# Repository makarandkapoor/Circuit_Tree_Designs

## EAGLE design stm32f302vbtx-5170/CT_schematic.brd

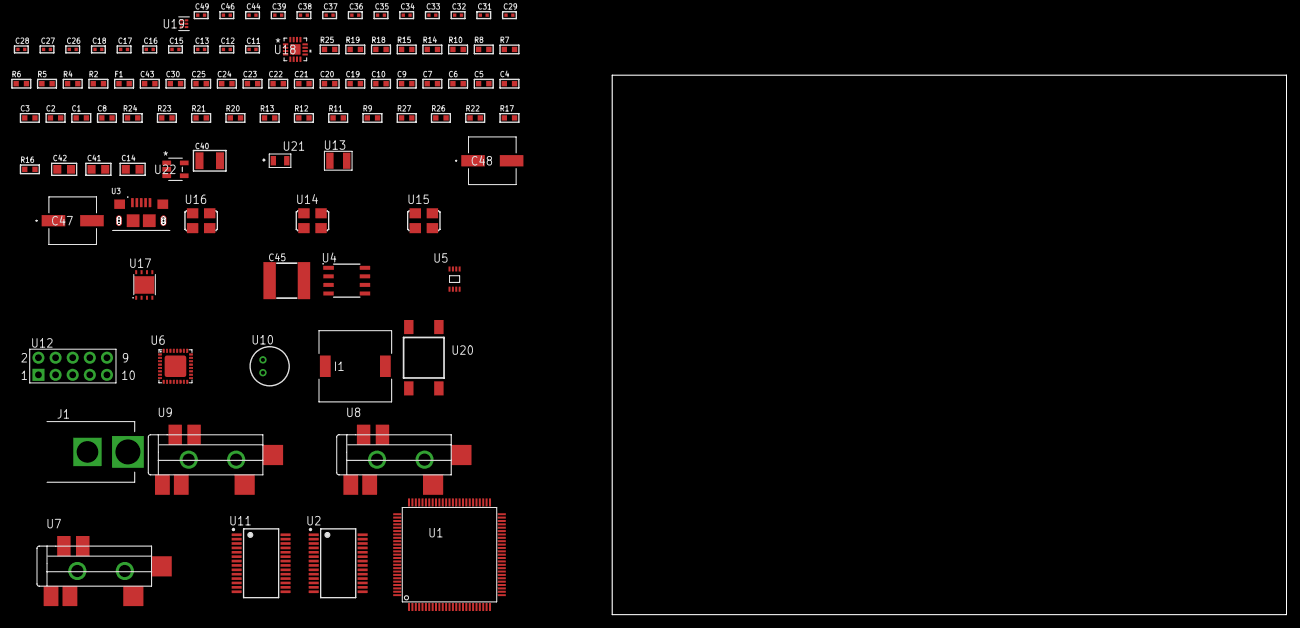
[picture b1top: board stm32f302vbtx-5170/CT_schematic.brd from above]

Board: 2 copper layers, 99 parts (0 on the bottom side), 69 nets, no tracks yet.

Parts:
C1, C10, C19, C20, C21, C22, C23, C24, C25, C30, C43: 1e-06; C0603
C2, C3, C4, C5, C6, C7: 1e-07; C0603
C8: 4.7e-06; C0603
C9: 1e-08; C0603
C11, C12: 1e-11; C0402
C13, C15, C16, C26, C27, C28, C29, C31, C32, C33, C34, C35, C44, C46: 1e-07; C0402
C14: 4.7e-06; C0805
C17, C18, C36, C37, C38, C39, C49: 1e-08; C0402
C40: 1e-05; C1210
C41, C42: 1e-05; C0805
C45: 6.8e-05; 2220
C47, C48: 0.0001; EXV-9H
F1: 240.0; L0603
I1: 5.2e-06; DR1040
J1: PJ-037B; PJ-037B_PACKAGE
R2, R19: 1000.0; R0603
R4, R10: 4700.0; R0603
R5, R6, R7, R8: 2200.0; R0603
R9, R11, R12, R13, R23, R24: 10000.0; R0603
R14, R15: 1270.0; R0603
R16, R17: 100000.0; R0603
R18: 200.0; R0603
R20: 20000.0; R0603
R21: 91000.0; R0603
R22: 300000.0; R0603
R25: 9100.0; R0603
R26: 680000.0; R0603
R27: 120000.0; R0603
U1: STM32F302VBT7; LQFP100
U2: FT232RL-REEL; SSOP-28
U3: 10118193-0001LF; FCI_10118193-0001LF
U4: M24M02-DRMN6TP; SOIC-8
U5: 24AA08T-I/MNY; TDFN-8/6MM
U6: SGTL5000XNAA3; QFN-32
U7, U8, U9: SJ-43515TS-SMT-TR
U10: WM-64PCT; WM-64PC
U11: ST3241EBPR; SSOP-28
U12: HTSS-105-01-G-D
U13: ABS07-32.768KHZ-7-T
U14: ASFL1-12MHZ-NCS; ASFL1
U15: ASFL-24.57MHZ-NCS; ASFL1
U16: ASFL1-25MHZ-NCS; ASFL1
U17: LP3878SDX-ADJ/NOPB; WSON-8
U18: LTC3601EUD#PBF; QFN-16_EP
U19: TPS3895ADRYR; SON-6
U20: 4-1437565-2; SW_4-1437565-2
U21: Q65110A2395; LGM67K-G1J2-24-Z
U22: nc7sz125m5x; NC7SZ125M5X

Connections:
CLK_CRYSTAL_U1_8: C11.1, U1.8, U13.1
CLK_CRYSTAL_U1_9: C12.1, U1.9, U13.2
CLK_U1_12: U1.12, U16.3
CLK_U2_27: U2.27, U14.3
CLK_U6_21: U6.21, U15.3
GND: C1.2, C2.2, C3.2, C4.2, C5.2, C6.2, C7.2, C8.2, C9.2, C10.2, C11.2, C12.2, C13.2, C14.2, C15.2, C16.2, C17.2, C18.2, C26.2, C27.2, C28.2, C29.2, C30.2, C31.2, C34.2, C35.2, C36.2, C37.2, C38.2, C39.2, C40.2, C41.2, C42.2, C43.2, C45.1, C45.2, C46.2, C47.2, C48.2, C49.2, J1.2, R2.2, R9.2, R12.2, R13.2, R15.2, R19.2, R20.2, R22.2, R25.2, R27.2, U1.20, U1.49, U1.74, U1.99, U2.7, U2.18, U2.21, U2.25, U2.26, U3.5, U3.6, U3.7, U3.8, U3.9, U4.4, U5.4, U5.7, U6.1, U6.3, U6.7, U6.EXP, U8.1, U9.1, U10.2, U11.23, U11.25, U12.9, U14.2, U15.2, U16.2, U17.3, U17.PAD, U18.1, U18.9, U18.17, U19.2, U21.C, U22.1, U22.3
NET_U1_13: R7.1, U1.13, U4.6
NET_U1_14: R4.1, U1.14, U22.4
NET_U1_22: C9.1, C10.1, F1.1, U1.21, U1.22
NET_U1_69: R8.1, U1.69, U4.5
NET_U1_76: R6.1, U1.76, U5.5
NET_U1_77: R5.1, U1.77, U5.6
NET_U1_94: R9.1, U1.94
NET_U1_98: U20.3, U20.4
NET_U2_14: R11.1, U2.14
NET_U2_17: C15.1, U2.17
NET_U2_19: R12.1, U2.19
NET_U3_1: R10.1, U3.1
NET_U3_2: U2.16, U3.2
NET_U3_3: U2.15, U3.3
NET_U4_3: R13.1, U4.3
NET_U6_10: C29.1, U6.10
NET_U6_29: R14.1, U6.29
NET_U6_31: R15.1, U6.31
NET_U7_1: U6.4, U7.1
NET_U7_2: U6.2, U7.2
NET_U7_5: U6.6, U7.5
NET_U8_2: C20.1, U8.2
NET_U8_5: C19.1, U8.5
NET_U9_2: C22.1, C23.1, U9.2
NET_U9_5: C21.1, U9.5
NET_U9_13: C22.2, C23.2
NET_U10_1: C24.1, C25.1, C30.1, U6.16, U10.1
NET_U10_15: C24.2, C25.2
NET_U11_1: C33.1, U11.1
NET_U11_2: C33.2, U11.2
NET_U11_3: C35.1, U11.3
NET_U11_22: R16.1, U11.22
NET_U11_24: C32.2, U11.24
NET_U11_27: C34.1, U11.27
NET_U11_28: C32.1, U11.28
NET_U12_3: U11.4, U12.3
NET_U12_4: U11.5, U12.4
NET_U12_5: U11.9, U12.5
NET_U12_6: U11.10, U12.6
NET_U17_1: C39.1, U17.1
NET_U17_6: R18.2, R19.1, U17.6
NET_U17_8: R17.1, U17.8
NET_U18_3: C44.2, I1.1, U18.3, U18.4
NET_U18_6: C44.1, U18.6
NET_U18_7: C43.1, U18.7, U18.12
NET_U18_10: R22.1, U18.10
NET_U18_11: R20.1, R21.1, U18.11
NET_U18_ATNET_3: I1.2, R21.2
NET_U19_1: R24.1, R25.1, U19.1
NET_U19_3: R26.2, R27.1, U19.3
NET_U19_4: R23.1, U19.4, U22.2
NET_U20_1: R2.1, U20.1, U20.2
PROC_I2S2_CK: U1.52, U6.24
PROC_I2S2_EXT_SD: U1.53, U6.25
PROC_I2S2_SD: U1.54, U6.26
PROC_I2S2_WS: U1.51, U6.23
PROC_UART4_RX: U1.79, U11.19
PROC_UART4_TX: U1.78, U11.14
PROC_UART5_RX: U1.83, U2.1
PROC_UART5_TX: U1.80, U2.5
VCC_S1_11V8: C40.1, C42.1, C47.1, C48.1, J1.1, R17.2, U17.4, U18.15, U18.16
VCC_TIER1_1V2: C26.1, C41.1, R18.1, U6.30, U17.5
VCC_TIER1_3V3: C1.1, C2.1, C3.1, C4.1, C5.1, C6.1, C7.1, C8.1, C13.1, C14.1, C16.1, C17.1, C18.1, C27.1, C28.1, C31.1, C36.1, C37.1, C38.1, C45.2, C46.1, C49.1, F1.2, I1.2, R4.2, R5.2, R6.2, R7.2, R8.2, R11.2, R14.2, R16.2, R21.2, R23.2, R24.2, R26.1, U1.6, U1.28, U1.50, U1.75, U1.100, U2.4, U2.20, U4.8, U5.8, U6.5, U6.20, U11.26, U14.4, U15.4, U16.4, U18.8, U19.6, U22.5

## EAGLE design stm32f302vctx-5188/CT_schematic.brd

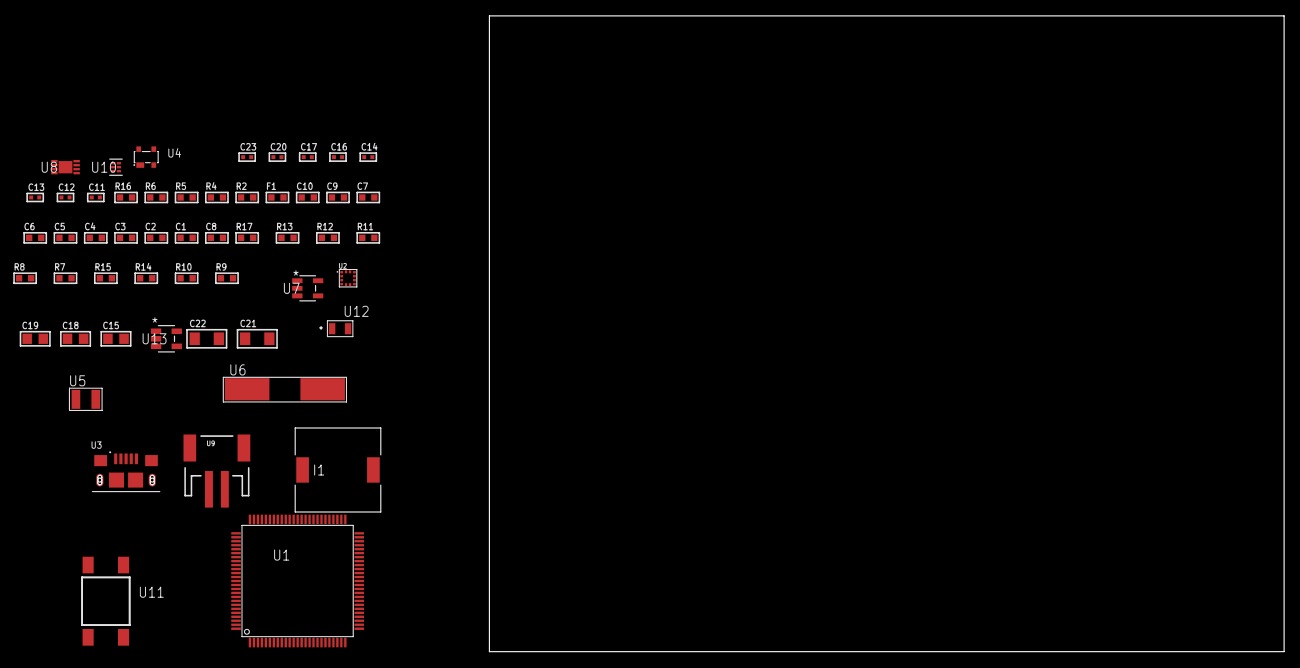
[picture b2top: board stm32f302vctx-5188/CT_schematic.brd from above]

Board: 2 copper layers, 149.3 x 80.0 mm, 53 parts (0 on the bottom side), 26 nets, no tracks yet.

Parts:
C1, C10: 1e-06; C0603
C2, C3, C4, C5, C6, C7: 1e-07; C0603
C8: 4.7e-06; C0603
C9: 1e-08; C0603
C11, C12, C13, C14: 1e-11; C0402
C15, C18, C19: 1e-05; C0805
C16, C17, C20: 1e-07; C0402
C21, C22: 1e-05; C1206
C23: 1e-08; C0402
F1: 240.0; L0603
I1: 5.2e-06; DR1040
R2: 1000.0; R0603
R4: 4700.0; R0603
R5, R6: 2200.0; R0603
R7, R8, R11, R12, R17: 10000.0; R0603
R9: 309473.68421053; R0603
R10: 1000000.0; R0603
R13: 18000.0; R0603
R14: 470000.0; R0603
R15: 120000.0; R0603
R16: 2000.0; R0603
U1: STM32F302VCT6; LQFP100
U2: LIS2HH12TR; LGA-12
U3: 10118193-0001LF; FCI_10118193-0001LF
U4: prtr5v0u2ax; SOT143B
U5: ABS07-32.768KHZ-7-T
U6: ABLS-25.000MHZ-B2F-T
U7: ltc3406es5; TSOT-23-5
U8: MCP73831T-2ACI/MC; DFN8_2X3MC
U9: S2B-PH-SM4-TB(LF)(SN); JST-2-SMD
U10: TPS3895ADRYR; SON-6
U11: 4-1437565-2; SW_4-1437565-2
U12: Q65110A2395; LGM67K-G1J2-24-Z
U13: nc7sz125m5x; NC7SZ125M5X

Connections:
CLK_CRYSTAL_U1_8: C11.1, U1.8, U5.1
CLK_CRYSTAL_U1_9: C12.1, U1.9, U5.2
CLK_CRYSTAL_U1_12: C13.1, U1.12, U6.1
CLK_CRYSTAL_U1_13: C14.1, U1.13, U6.2
GND: C1.2, C2.2, C3.2, C4.2, C5.2, C6.2, C7.2, C8.2, C9.2, C10.2, C11.2, C12.2, C13.2, C14.2, C15.2, C16.2, C17.2, C18.2, C19.1, C19.2, C20.2, C21.2, C22.2, C23.2, R2.2, R7.2, R9.2, R13.2, R15.2, R16.2, U1.20, U1.49, U1.74, U1.99, U2.5, U2.6, U2.7, U2.8, U3.5, U3.6, U3.7, U3.8, U3.9, U4.1, U7.2, U8.6, U8.9, U9.2, U10.2, U12.C, U13.1, U13.3
INPUT_USBPOWER_5V: C21.1, R17.2, U3.1, U4.4, U8.1, U8.2
NET_U1_14: R4.1, U1.14, U13.4
NET_U1_22: C9.1, C10.1, F1.1, U1.21, U1.22
NET_U1_76: R6.1, U1.76, U2.4
NET_U1_77: R5.1, U1.77, U2.1
NET_U1_94: R7.1, U1.94
NET_U1_98: U11.3, U11.4
NET_U2_2: R8.1, U2.2
NET_U7_3: I1.1, U7.3
NET_U7_5: R9.1, R10.1, U7.5
NET_U7_ATNET_3: I1.2, R10.2
NET_U8_5: R17.1, U8.5
NET_U8_8: R16.1, U8.8
NET_U10_1: R12.1, R13.1, U10.1
NET_U10_3: R14.2, R15.1, U10.3
NET_U10_4: R11.1, U10.4, U13.2
NET_U11_1: R2.1, U11.1, U11.2
PROC_USB_DM: U1.70, U3.2, U4.3
PROC_USB_DP: U1.71, U3.3, U4.2
VCC_S1_3V7: C18.1, C22.1, U7.4, U8.3, U8.4, U9.1
VCC_TIER1_2V5: C1.1, C2.1, C3.1, C4.1, C5.1, C6.1, C7.1, C8.1, C15.1, C16.1, C17.1, C19.2, C20.1, C23.1, F1.2, I1.2, R4.2, R5.2, R6.2, R8.2, R10.2, R11.2, R12.2, R14.1, U1.6, U1.28, U1.50, U1.75, U1.100, U2.9, U2.10, U10.6, U13.5

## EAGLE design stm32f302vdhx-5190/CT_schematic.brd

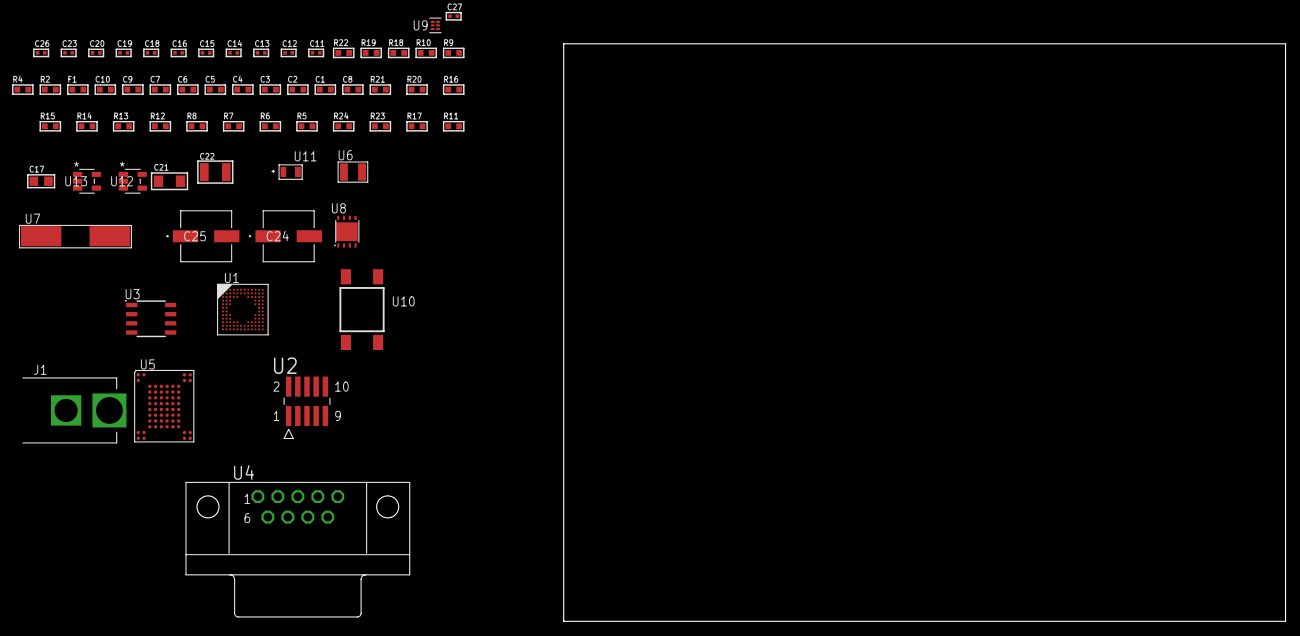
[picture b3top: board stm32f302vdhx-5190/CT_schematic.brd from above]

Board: 2 copper layers, 100.0 x 80.0 mm, 64 parts (0 on the bottom side), 42 nets, no tracks yet.

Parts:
C1, C10: 1e-06; C0603
C2, C3, C4, C5, C6, C7: 1e-07; C0603
C8: 4.7e-06; C0603
C9: 1e-08; C0603
C11, C12, C13, C14: 1e-11; C0402
C15, C16, C18, C19, C23: 1e-07; C0402
C17: 1e-05; C0805
C20, C26, C27: 1e-08; C0402
C21: 1e-05; C1206
C22: 1e-05; C1210
C24, C25: 0.0001; EXV-9H
F1: 240.0; L0603
J1: PJ-037B; PJ-037B_PACKAGE
R2, R19: 1000.0; R0603
R4: 4700.0; R0603
R5, R6, R7, R8, R12, R13, R14, R15, R16, R20, R21: 10000.0; R0603
R9: 5.0; R0603
R10: 120.0; R0603
R11, R17: 100000.0; R0603
R18: 2231.0; R0603
R22: 9100.0; R0603
R23: 680000.0; R0603
R24: 120000.0; R0603
U1: STM32F302VDH6; UFBGA100
U2: FTSH-105-01-L-DV-K; SAMTEC_FTSH-105-01-L-DV-K
U3: SN65HVD230D; SOIC-8
U4: 182-009-113R531; 182-009-MALE
U5: TH58NVG3S0HBAI4
U6: ABS07-32.768KHZ-7-T
U7: ABLS-25.000MHZ-B2F-T
U8: LP3878SDX-ADJ/NOPB; WSON-8
U9: TPS3895ADRYR; SON-6
U10: 4-1437565-2; SW_4-1437565-2
U11: Q65110A2395; LGM67K-G1J2-24-Z
U12, U13: nc7sz125m5x; NC7SZ125M5X

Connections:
CLK_CRYSTAL_U1_D1: C11.1, U1.D1, U6.1
CLK_CRYSTAL_U1_E1: C12.1, U1.E1, U6.2
CLK_CRYSTAL_U1_F1: C13.1, U1.F1, U7.1
CLK_CRYSTAL_U1_G1: C14.1, U1.G1, U7.2
GND: C1.2, C2.2, C3.2, C4.2, C5.2, C6.2, C7.2, C8.2, C9.2, C10.2, C11.2, C12.2, C13.2, C14.2, C15.2, C16.2, C17.2, C18.2, C19.2, C20.2, C21.2, C22.2, C23.2, C24.2, C25.2, C26.2, C27.2, J1.2, R2.2, R5.2, R9.2, R11.2, R19.2, R22.2, R24.2, U1.D3, U1.E3, U1.F11, U1.F12, U1.K1, U2.3, U2.5, U3.2, U4.5, U5.C5, U5.K3, U5.K8, U8.3, U8.PAD, U9.2, U11.C, U12.2, U12.3, U13.1, U13.3
NET_U1_A4: R5.1, U1.A4
NET_U1_H2: R4.1, U1.H2, U13.4
NET_U1_L1: C9.1, C10.1, F1.1, U1.L1, U1.M1
NET_U1_M12: U10.3, U10.4
NET_U2_9: R9.1, U2.9
NET_U3_6: R10.2, U3.6
NET_U3_8: R11.1, U3.8
NET_U4_2: R10.2, U3.6, U4.2
NET_U4_3: R10.1, U3.7, U4.3
NET_U5_C3: R15.1, U5.C3
NET_U5_C8: R16.1, U5.C8
NET_U8_1: C20.1, U8.1
NET_U8_6: R18.2, R19.1, U8.6
NET_U8_8: R17.1, U8.8
NET_U9_1: R21.1, R22.1, U9.1
NET_U9_3: R23.2, R24.1, U9.3
NET_U9_4: R20.1, U9.4, U12.4, U13.2
NET_U10_1: R2.1, U10.1, U10.2
PROC_CAN_RX: U1.A3, U3.4
PROC_CAN_TX: U1.A12, U3.1
PROC_FMC_D0: U1.H11, U5.H4
PROC_FMC_D1: U1.H10, U5.J4
PROC_FMC_D2: U1.C9, U5.K4
PROC_FMC_D3: U1.B9, U5.K5
PROC_FMC_D4: U1.M7, U5.K6
PROC_FMC_D5: U1.L7, U5.J7
PROC_FMC_D6: U1.M8, U5.K7
PROC_FMC_D7: U1.L8, U5.J8
PROC_FMC_NCE2: R12.1, U1.A5, U5.C6
PROC_FMC_NOE: R13.1, U1.B7, U5.D4
PROC_FMC_NWE: R14.1, U1.A6, U5.C7
PROC_SYS_JTCK_SWCLK: R7.1, U1.A10, U2.4
PROC_SYS_JTDO_TRACESWO: U1.A8, U2.6
PROC_SYS_JTMS_SWDIO: R8.1, U1.A11, U2.2
RST_OUT_U2_JTAG_RST_B: R6.1, U2.10, U12.1
VCC_S1_10V1: C21.1, C24.1, C25.1, J1.1, R17.2, U8.4
VCC_TIER1_3V3: C1.1, C2.1, C3.1, C4.1, C5.1, C6.1, C7.1, C8.1, C15.1, C16.1, C17.1, C18.1, C19.1, C22.1, C23.1, C26.1, C27.1, F1.2, R4.2, R6.2, R7.2, R8.2, R12.2, R13.2, R14.2, R15.2, R16.2, R18.1, R20.2, R21.2, R23.1, U1.C4, U1.E2, U1.G11, U1.G12, U1.H3, U2.1, U3.3, U5.H8, U5.J6, U8.5, U9.6, U12.5, U13.5

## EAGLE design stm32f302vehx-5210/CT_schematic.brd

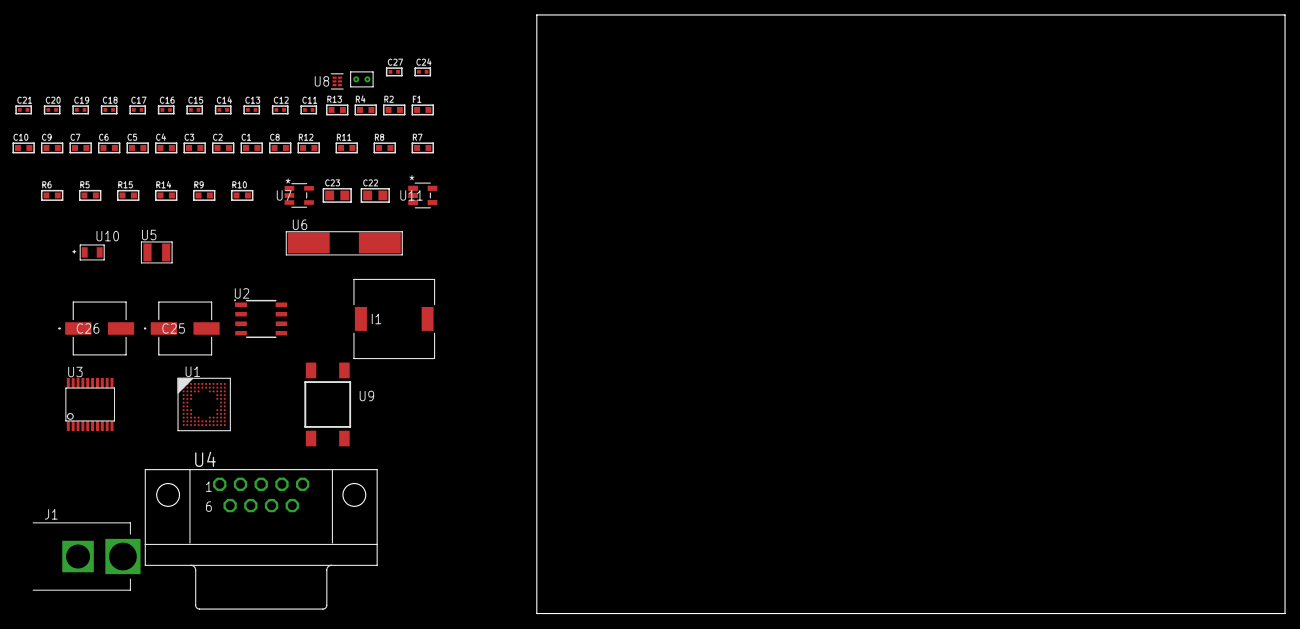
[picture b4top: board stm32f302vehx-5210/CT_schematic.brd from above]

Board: 2 copper layers, 100.0 x 80.0 mm, 55 parts (0 on the bottom side), 37 nets, no tracks yet.

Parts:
C1, C10: 1e-06; C0603
C2, C3, C4, C5, C6, C7: 1e-07; C0603
C8: 4.7e-06; C0603
C9: 1e-08; C0603
C11, C12, C13, C14: 1e-11; C0402
C15, C27: 1e-08; C0402
C16, C17, C18, C19, C20, C21, C24: 1e-07; C0402
C22, C23: 1e-05; C0805
C25, C26: 0.0001; EXV-9H
F1: 240.0; L0603
I1: 5.2e-06; DR1040
J1: PJ-037B; PJ-037B_PACKAGE
R2: 1000.0; R0603
R4: 4700.0; R0603
R5, R6, R7, R8, R11, R12: 10000.0; R0603
R9: 220000.0; R0603
R10: 1000000.0; R0603
R13: 9100.0; R0603
R14: 680000.0; R0603
R15: 120000.0; R0603
U1: STM32F302VEH6; UFBGA100
U2: AT25256B-SSHL-T; SOIC-8
U3: SP3203ECY-L/TR; TSSOP20-I
U4: 182-009-113R531; 182-009-MALE
U5: ABS07-32.768KHZ-7-T
U6: ABLS-25.000MHZ-B2F-T
U7: ltc3406es5; TSOT-23-5
U8: TPS3895ADRYR; SON-6
U9: 4-1437565-2; SW_4-1437565-2
U10: Q65110A2395; LGM67K-G1J2-24-Z
U11: nc7sz125m5x; NC7SZ125M5X
U12: Dummy; DUMMY_PACKAGE_112

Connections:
CLK_CRYSTAL_U1_D1: C11.1, U1.D1, U5.1
CLK_CRYSTAL_U1_E1: C12.1, U1.E1, U5.2
CLK_CRYSTAL_U1_F1: C13.1, U1.F1, U6.1
CLK_CRYSTAL_U1_G1: C14.1, U1.G1, U6.2
GND: C1.2, C2.2, C3.2, C4.2, C5.2, C6.2, C7.2, C8.2, C9.2, C10.2, C11.2, C12.2, C13.2, C14.2, C15.2, C16.2, C17.2, C20.2, C21.2, C22.2, C23.1, C23.2, C24.2, C25.2, C26.2, C27.2, J1.2, R2.2, R5.2, R9.2, R13.2, R15.2, U1.D3, U1.E3, U1.F11, U1.F12, U1.K1, U2.4, U3.18, U4.5, U7.2, U8.2, U10.C, U11.1, U11.3, U12.1
NET_U1_A4: R5.1, U1.A4
NET_U1_H2: R4.1, U1.H2, U11.4
NET_U1_L1: C9.1, C10.1, F1.1, U1.L1, U1.M1
NET_U1_M12: U9.3, U9.4
NET_U2_3: R6.1, U2.3
NET_U2_7: R8.1, U2.7
NET_U3_1: C18.1, U3.1
NET_U3_2: C20.1, U3.2
NET_U3_3: C18.2, U3.3
NET_U3_4: C19.1, U3.4
NET_U3_5: C19.2, U3.5
NET_U3_6: C21.1, U3.6
NET_U4_2: U3.14, U4.2
NET_U4_3: U3.17, U4.3
NET_U4_7: U3.13, U4.7
NET_U4_8: U3.16, U4.8
NET_U7_3: I1.1, U7.3
NET_U7_5: R9.1, R10.1, U7.5
NET_U7_ATNET_3: I1.2, R10.2
NET_U8_1: R12.1, R13.1, U8.1
NET_U8_3: R14.2, R15.1, U8.3
NET_U8_4: R11.1, U8.4, U11.2
NET_U9_1: R2.1, U9.1, U9.2
PROC_DAC1_OUT1: U1.M3, U12.2
PROC_SPI1_MISO: U1.A7, U2.2
PROC_SPI1_MOSI: U1.C5, U2.5
PROC_SPI1_NSS: R7.1, U1.A9, U2.1
PROC_SPI1_SCK: U1.A8, U2.6
PROC_UART4_RX: U1.C10, U3.11
PROC_UART4_TX: U1.B11, U3.7
VCC_S1_4V9: C22.1, C25.1, C26.1, J1.1, U7.4
VCC_TIER1_3V3: C1.1, C2.1, C3.1, C4.1, C5.1, C6.1, C7.1, C8.1, C15.1, C16.1, C17.1, C23.2, C24.1, C27.1, F1.2, I1.2, R4.2, R6.2, R7.2, R8.2, R10.2, R11.2, R12.2, R14.1, U1.C4, U1.E2, U1.G11, U1.G12, U1.H3, U2.8, U3.12, U3.19, U8.6, U11.5

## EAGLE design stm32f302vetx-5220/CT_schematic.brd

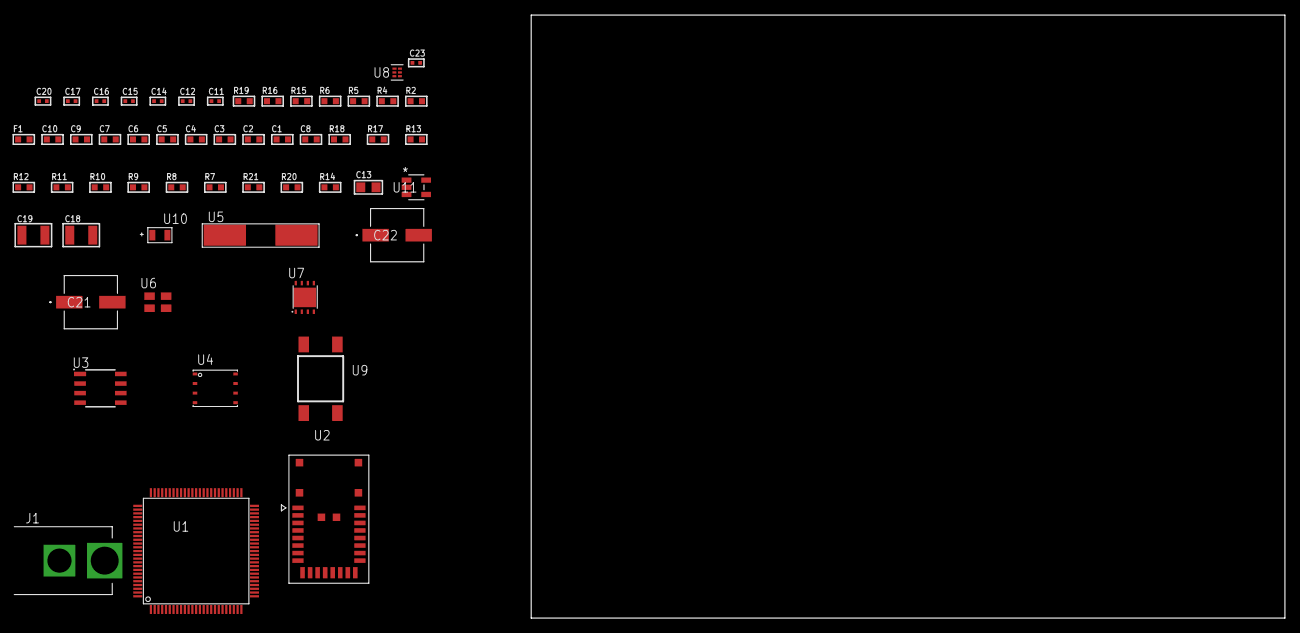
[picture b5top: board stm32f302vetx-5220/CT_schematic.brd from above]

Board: 2 copper layers, 100.0 x 80.0 mm, 55 parts (0 on the bottom side), 29 nets, no tracks yet.

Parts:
C1, C10: 1e-06; C0603
C2, C3, C4, C5, C6, C7: 1e-07; C0603
C8: 4.7e-06; C0603
C9: 1e-08; C0603
C11, C12: 1e-11; C0402
C13: 1e-05; C0805
C14, C15, C16, C17, C23: 1e-08; C0402
C18, C19: 1e-05; C1210
C20: 1e-07; C0402
C21, C22: 0.0001; EXV-9H
F1: 240.0; L0603
J1: PJ-037B; PJ-037B_PACKAGE
R2, R16: 1000.0; R0603
R4: 4700.0; R0603
R5, R6: 2200.0; R0603
R7, R8, R9, R10, R11, R12, R13, R17, R18: 10000.0; R0603
R14: 100000.0; R0603
R15: 2231.0; R0603
R19: 9100.0; R0603
R20: 680000.0; R0603
R21: 120000.0; R0603
U1: STM32F302VET6; LQFP100
U2: A2500R24A00GM
U3: AT25M01-SSHM-T; SOIC-8
U4: 24AA512-I/MF; DFN8-S
U5: ABLS-25.000MHZ-B2F-T
U6: ASEK-32.768KHz-ECST; ASEK
U7: LP3878SDX-ADJ/NOPB; WSON-8
U8: TPS3895ADRYR; SON-6
U9: 4-1437565-2; SW_4-1437565-2
U10: Q65110A2395; LGM67K-G1J2-24-Z
U11: nc7sz125m5x; NC7SZ125M5X

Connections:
CLK_CRYSTAL_U1_12: C11.1, U1.12, U5.1
CLK_CRYSTAL_U1_13: C12.1, U1.13, U5.2
CLK_U1_8: U1.8, U6.3
GND: C1.2, C2.2, C3.2, C4.2, C5.2, C6.2, C7.2, C8.2, C9.2, C10.2, C11.2, C12.2, C13.2, C14.2, C15.2, C16.2, C17.2, C18.2, C19.2, C20.2, C21.2, C22.2, C23.2, J1.2, R2.2, R7.2, R11.2, R12.2, R16.2, R19.2, R21.2, U1.20, U1.27, U1.49, U1.74, U1.99, U2.8, U2.17, U3.4, U4.4, U4.7, U6.2, U7.3, U7.PAD, U8.2, U10.C, U11.1, U11.3
NET_U1_14: R4.1, U1.14, U11.4
NET_U1_22: C9.1, C10.1, F1.1, U1.21, U1.22
NET_U1_76: R6.1, U1.76, U4.5
NET_U1_77: R5.1, U1.77, U4.6
NET_U1_94: R7.1, U1.94
NET_U1_98: U9.3, U9.4
NET_U3_3: R8.1, U3.3
NET_U3_7: R10.1, U3.7
NET_U4_1: R11.1, U4.1
NET_U4_2: R12.1, U4.2
NET_U4_3: R13.1, U4.3
NET_U7_1: C17.1, U7.1
NET_U7_6: R15.2, R16.1, U7.6
NET_U7_8: R14.1, U7.8
NET_U8_1: R18.1, R19.1, U8.1
NET_U8_3: R20.2, R21.1, U8.3
NET_U8_4: R17.1, U8.4, U11.2
NET_U9_1: R2.1, U9.1, U9.2
PROC_SPI1_MISO: U1.31, U2.10
PROC_SPI1_MOSI: U1.32, U2.11
PROC_SPI1_NSS: U1.29, U2.12
PROC_SPI1_SCK: U1.30, U2.9
PROC_SPI2_NSS: R9.1, U3.1
VCC_S1_11V3: C18.1, C21.1, C22.1, J1.1, R14.2, U7.4
VCC_TIER1_3V3: C1.1, C2.1, C3.1, C4.1, C5.1, C6.1, C7.1, C8.1, C13.1, C14.1, C15.1, C16.1, C19.1, C20.1, C23.1, F1.2, R4.2, R5.2, R6.2, R8.2, R9.2, R10.2, R13.2, R15.1, R17.2, R18.2, R20.1, U1.6, U1.28, U1.50, U1.75, U1.100, U2.18, U3.8, U4.8, U6.4, U7.5, U8.6, U11.5

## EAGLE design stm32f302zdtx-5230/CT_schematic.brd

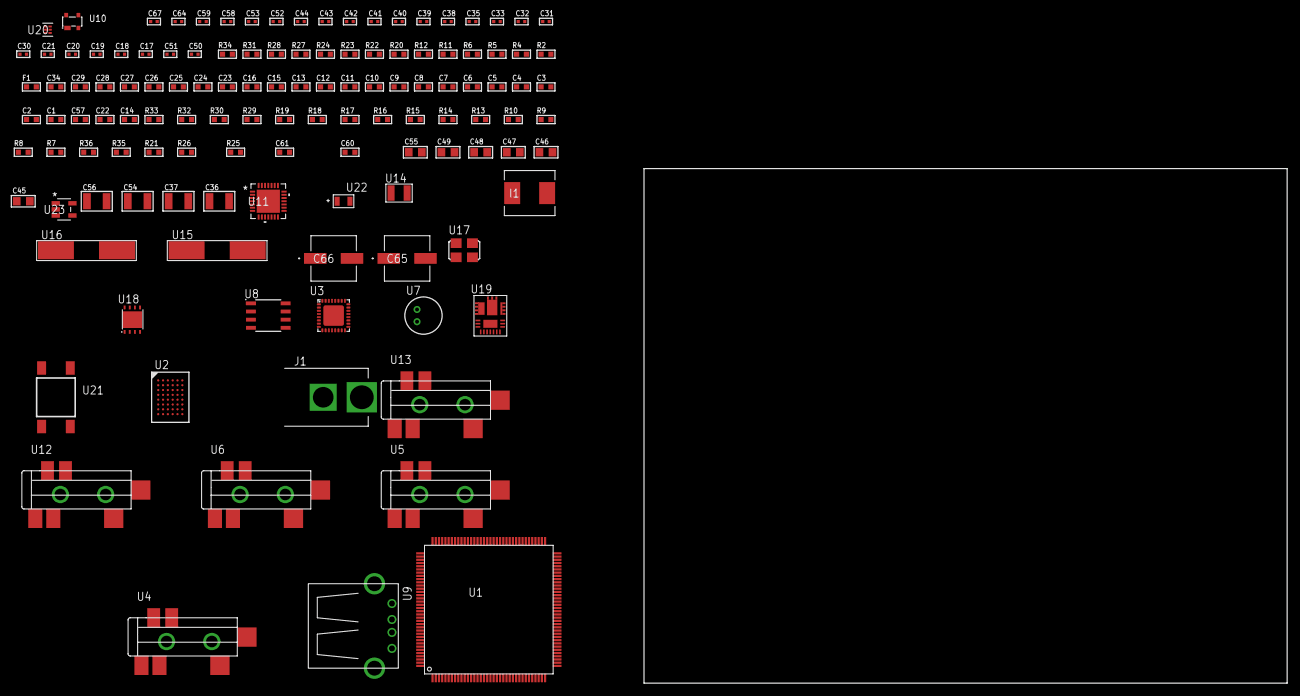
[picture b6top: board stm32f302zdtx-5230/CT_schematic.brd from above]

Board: 2 copper layers, 100.0 x 80.0 mm, 125 parts (0 on the bottom side), 104 nets, no tracks yet.

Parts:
C1, C16, C23, C24, C25, C26, C27, C28, C29, C34: 1e-06; C0603
C2, C3, C4, C5, C6, C7, C8, C9, C10, C11, C12, C13: 1e-07; C0603
C14: 4.7e-06; C0603
C15: 1e-08; C0603
C17, C18, C19, C20: 1e-11; C0402
C21, C30, C31, C32, C33, C35, C40, C41, C42, C43, C44, C58, C59, C64: 1e-07; C0402
C22, C57: 2.2e-06; C0603
C36, C37: 2.2e-05; C1210
C38, C39: 1e-09; C0402
C45, C46, C47, C48, C49, C55: 1e-05; C0805
C50, C51: 2.2e-11; C0402
C52, C53, C67: 1e-08; C0402
C54: 1e-05; C1210
C56: 0.0001; C1210
C60: 6.9887470079922e-09; R0603
C61: 2.3825273890883e-07; R0603
C65, C66: 0.0001; EXV-9H
F1: 240.0; L0603
I1: 6.8e-07; IND25X25CZ
J1: PJ-037B; PJ-037B_PACKAGE
R2, R23: 1000.0; R0603
R4: 4700.0; R0603
R5, R6: 2200.0; R0603
R7, R8, R9, R10, R13, R14, R15, R16, R32, R33: 10000.0; R0603
R11, R12: 1270.0; R0603
R17, R18, R19: 47000.0; R0603
R20: 680.0; R0603
R21: 100000.0; R0603
R22: 200.0; R0603
R24: 0.1; R0603
R25: 4030.2416170974; R0603
R26: 719.68600305311; R0603
R27: 75.0; R0603
R28: 130.0; R0603
R29: 39000.0; R0603
R30: 49900.0; R0603
R31: 5760.0; R0603
R34: 9100.0; R0603
R35: 680000.0; R0603
R36: 120000.0; R0603
U1: STM32F302ZDT7; LQFP144
U2: CY62147GE30-45BVXI; VFBGA48
U3: SGTL5000XNAA3; QFN-32
U4, U5, U6, U12, U13: SJ-43515TS-SMT-TR
U7: WM-64PCT; WM-64PC
U8: TMP75BID; SOIC-8
U9: 61400416021; USB-A-H
U10: prtr5v0u2ax; SOT143B
U11: WM8731CLSEFL; QFN-28
U14: ABS07-32.768KHZ-7-T
U15: ABLS-25.000MHZ-B2F-T
U16: ABLS-12.288MHZ-B4-T
U17: ASFL-24.57MHZ-NCS; ASFL1
U18: LP3878SDX-ADJ/NOPB; WSON-8
U19: IR3899MTR1PBF
U20: TPS3895ADRYR; SON-6
U21: 4-1437565-2; SW_4-1437565-2
U22: Q65110A2395; LGM67K-G1J2-24-Z
U23: nc7sz125m5x; NC7SZ125M5X

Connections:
CLK_CRYSTAL_U1_8: C17.1, U1.8, U14.1
CLK_CRYSTAL_U1_9: C18.1, U1.9, U14.2
CLK_CRYSTAL_U1_23: C19.1, U1.23, U15.1
CLK_CRYSTAL_U1_24: C20.1, U1.24, U15.2
CLK_CRYSTAL_U11_1: C50.1, U11.1, U16.1
CLK_CRYSTAL_U11_2: C51.1, U11.2, U16.2
CLK_U3_21: U3.21, U17.3
GND: C1.2, C2.2, C3.2, C4.2, C5.2, C6.2, C7.2, C8.2, C9.2, C10.2, C11.2, C12.2, C13.2, C14.2, C15.2, C16.2, C17.2, C18.2, C19.2, C20.2, C21.2, C22.2, C30.2, C31.2, C32.2, C33.2, C34.2, C35.2, C39.2, C40.2, C41.2, C42.2, C43.2, C44.2, C45.2, C46.2, C47.2, C48.2, C49.2, C50.2, C51.2, C52.2, C53.2, C54.2, C55.2, C57.2, C58.2, C59.2, C64.2, C65.2, C66.2, C67.2, J1.2, R2.2, R7.2, R12.2, R16.2, R17.2, R18.2, R19.2, R23.2, R24.1, R24.2, R26.2, R29.2, R31.2, R34.2, R36.2, U1.16, U1.30, U1.31, U1.38, U1.51, U1.61, U1.71, U1.83, U1.94, U1.107, U1.120, U1.130, U1.143, U2.D1, U2.E6, U3.1, U3.3, U3.7, U3.EXP, U5.1, U6.1, U7.2, U8.4, U9.4, U9.5, U9.6, U10.1, U11.4, U11.15, U11.19, U11.25, U11.26, U11.29, U12.1, U13.1, U17.2, U18.3, U18.PAD, U19.4, U19.11, U19.17, U20.2, U22.C, U23.1, U23.3
NET_U1_25: R4.1, U1.25, U23.4
NET_U1_33: C15.1, C16.1, F1.1, U1.32, U1.33
NET_U1_109: R6.1, U1.109, U8.1
NET_U1_110: R5.1, U1.110, U8.2
NET_U1_138: R7.1, U1.138
NET_U1_142: U21.3, U21.4
NET_U3_10: C33.1, U3.10
NET_U3_29: R11.1, U3.29
NET_U3_31: R12.1, U3.31
NET_U4_1: U3.4, U4.1
NET_U4_2: U3.2, U4.2
NET_U4_5: U3.6, U4.5
NET_U5_2: C24.1, U5.2
NET_U5_5: C23.1, U5.5
NET_U6_2: C26.1, C27.1, U6.2
NET_U6_5: C25.1, U6.5
NET_U6_13: C26.2, C27.2
NET_U7_1: C28.1, C29.1, C34.1, U3.16, U7.1
NET_U7_15: C28.2, C29.2
NET_U8_3: R13.1, U8.3
NET_U8_5: R16.1, U8.5
NET_U8_6: R15.1, U8.6
NET_U8_7: R14.1, U8.7
NET_U10_4: U9.1, U10.4
NET_U11_20: C44.1, C49.1, U11.20
NET_U12_2: C37.1, R18.1, U12.2
NET_U12_5: C36.1, R17.1, U12.5
NET_U13_5: C38.1, C39.1, R19.1, R20.1, U13.5
NET_U18_1: C53.1, U18.1
NET_U18_6: R22.2, R23.1, U18.6
NET_U18_8: R21.1, U18.8
NET_U19_1: C60.1, R25.1, R26.1, R27.1, R28.1, U19.1, U19.8
NET_U19_2: C59.1, U19.2
NET_U19_3: C60.2, C61.1, C61.2, U19.3
NET_U19_5: R29.1, U19.5
NET_U19_10: C57.1, U19.10
NET_U19_12: C56.1, I1.1, U19.12
NET_U19_14: C56.2, U19.14
NET_U19_15: R30.1, R31.1, U19.15
NET_U19_ATNET_3: I1.2, R25.2
NET_U19_ATNET_4: C61.2, R27.2
NET_U20_1: R33.1, R34.1, U20.1
NET_U20_3: R35.2, R36.1, U20.3
NET_U20_4: R32.1, U20.4, U23.2
NET_U21_1: R2.1, U21.1, U21.2
PROC_FMC_A0: U1.10, U2.A3
PROC_FMC_A1: U1.11, U2.A4
PROC_FMC_A2: U1.12, U2.A5
PROC_FMC_A3: U1.13, U2.B3
PROC_FMC_A4: U1.14, U2.B4
PROC_FMC_A5: U1.15, U2.C3
PROC_FMC_A6: U1.50, U2.C4
PROC_FMC_A7: U1.53, U2.D4
PROC_FMC_A8: U1.54, U2.H2
PROC_FMC_A9: U1.55, U2.H3
PROC_FMC_A10: U1.56, U2.H4
PROC_FMC_A11: U1.57, U2.H5
PROC_FMC_A12: U1.87, U2.G3
PROC_FMC_A13: U1.88, U2.G4
PROC_FMC_A14: U1.89, U2.F3
PROC_FMC_A15: U1.90, U2.F4
PROC_FMC_A16: U1.80, U2.E4
PROC_FMC_A17: U1.81, U2.D3
PROC_FMC_D0: U1.85, U2.B6
PROC_FMC_D1: U1.86, U2.C5
PROC_FMC_D2: U1.114, U2.C6
PROC_FMC_D3: U1.115, U2.D5
PROC_FMC_D4: U1.58, U2.E5
PROC_FMC_D5: U1.59, U2.F5
PROC_FMC_D6: U1.60, U2.F6
PROC_FMC_D7: U1.63, U2.G6
PROC_FMC_D8: U1.64, U2.B1
PROC_FMC_D9: U1.65, U2.C1
PROC_FMC_D10: U1.66, U2.C2
PROC_FMC_D11: U1.67, U2.D2
PROC_FMC_D12: U1.68, U2.E2
PROC_FMC_D13: U1.77, U2.F2
PROC_FMC_D14: U1.78, U2.F1
PROC_FMC_D15: U1.79, U2.G1
PROC_FMC_NBL0: U1.141, U2.A1
PROC_FMC_NE2: R9.1, U1.124, U2.B5
PROC_FMC_NOE: R8.1, U1.118, U2.A2
PROC_FMC_NWE: R10.1, U1.119, U2.G5
PROC_I2S2_CK: U1.74, U11.7
PROC_I2S2_EXT_SD: U1.75, U11.10
PROC_I2S2_SD: U1.76, U11.8
PROC_I2S2_WS: U1.73, U11.9, U11.11
PROC_I2S3_CK: U1.111, U3.24
PROC_I2S3_EXT_SD: U1.112, U3.25
PROC_I2S3_SD: U1.113, U3.26
PROC_I2S3_WS: U1.40, U3.23
PROC_USB_DM: U9.2, U10.3
PROC_USB_DP: U9.3, U10.2
VCC_S1_15V3: C54.1, C58.1, C65.1, C66.1, J1.1, R21.2, R30.2, U18.4, U19.9
VCC_TIER1_1V2: C30.1, C55.1, R22.1, U3.30, U18.5
VCC_TIER1_3V3: C1.1, C2.1, C3.1, C4.1, C5.1, C6.1, C7.1, C8.1, C9.1, C10.1, C11.1, C12.1, C13.1, C14.1, C21.1, C22.1, C31.1, C32.1, C35.1, C40.1, C41.1, C42.1, C43.1, C45.1, C46.1, C47.1, C48.1, C52.1, C64.1, C67.1, F1.2, I1.2, R4.2, R5.2, R6.2, R8.2, R9.2, R10.2, R11.2, R13.2, R14.2, R15.2, R25.2, R32.2, R33.2, R35.1, U1.6, U1.17, U1.39, U1.52, U1.62, U1.72, U1.84, U1.95, U1.108, U1.121, U1.131, U1.144, U2.D6, U2.E1, U3.5, U3.20, U8.8, U11.3, U11.5, U11.12, U11.18, U17.4, U20.6, U23.5

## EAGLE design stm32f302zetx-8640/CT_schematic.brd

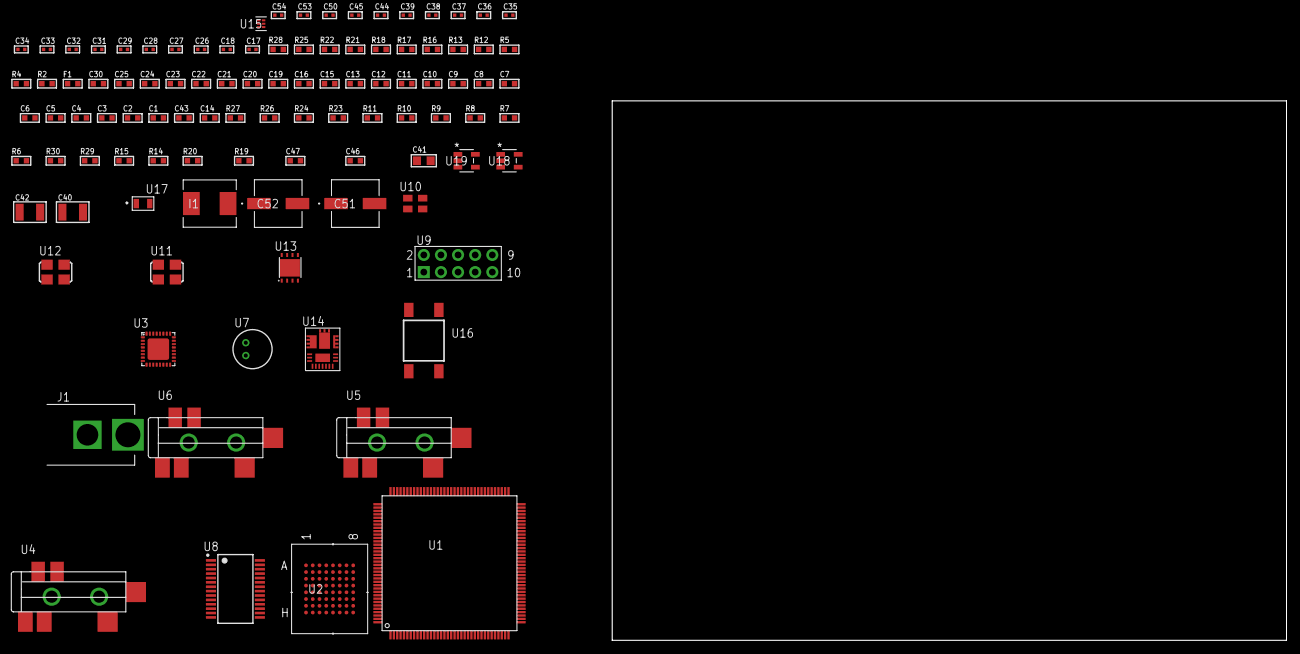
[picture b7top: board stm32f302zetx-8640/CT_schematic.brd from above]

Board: 2 copper layers, 100.0 x 80.0 mm, 102 parts (0 on the bottom side), 105 nets, no tracks yet.

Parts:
C1, C16, C19, C20, C21, C22, C23, C24, C25, C30: 1e-06; C0603
C2, C3, C4, C5, C6, C7, C8, C9, C10, C11, C12, C13: 1e-07; C0603
C14: 4.7e-06; C0603
C15: 1e-08; C0603
C17, C18, C36, C37, C38, C39, C53, C54: 1e-08; C0402
C26, C27, C28, C29, C31, C32, C33, C34, C35, C44, C45, C50: 1e-07; C0402
C40: 1e-05; C1210
C41: 1e-05; C0805
C42: 0.0001; C1210
C43: 2.2e-06; C0603
C46: 7.6008333472543e-09; R0603
C47: 2.591193186564e-07; R0603
C51, C52: 0.0001; EXV-9H
F1: 240.0; L0603
I1: 6.8e-07; IND25X25CZ
J1: PJ-037B; PJ-037B_PACKAGE
R2, R17: 1000.0; R0603
R4, R5: 4700.0; R0603
R6, R7, R8, R9, R10, R11, R26, R27: 10000.0; R0603
R12, R13: 1270.0; R0603
R14, R15: 100000.0; R0603
R16: 200.0; R0603
R18: 0.1; R0603
R19: 4030.2416170974; R0603
R20: 719.68600305311; R0603
R21: 68.0; R0603
R22: 130.0; R0603
R23: 39000.0; R0603
R24: 49900.0; R0603
R25: 5760.0; R0603
R28: 9100.0; R0603
R29: 680000.0; R0603
R30: 120000.0; R0603
U1: STM32F302ZET6; LQFP144
U2: mt28ew256aba1HPC-0SIT; LBGA-64
U3: SGTL5000XNAA3; QFN-32
U4, U5, U6: SJ-43515TS-SMT-TR
U7: WM-64PCT; WM-64PC
U8: ST3241EBPR; SSOP-28
U9: HTSS-105-01-G-D
U10: ASEK-32.768KHz-ECST; ASEK
U11: ASFL-24.57MHZ-NCS; ASFL1
U12: ASFL1-25MHZ-NCS; ASFL1
U13: LP3878SDX-ADJ/NOPB; WSON-8
U14: IR3899MTR1PBF
U15: TPS3895ADRYR; SON-6
U16: 4-1437565-2; SW_4-1437565-2
U17: Q65110A2395; LGM67K-G1J2-24-Z
U18, U19: nc7sz125m5x; NC7SZ125M5X

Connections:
CLK_U1_8: U1.8, U10.3
CLK_U1_23: U1.23, U12.3
CLK_U3_21: U3.21, U11.3
GND: C1.2, C2.2, C3.2, C4.2, C5.2, C6.2, C7.2, C8.2, C9.2, C10.2, C11.2, C12.2, C13.2, C14.2, C15.2, C16.2, C17.2, C18.2, C26.2, C27.2, C28.2, C29.2, C30.2, C31.2, C34.2, C35.2, C36.2, C37.2, C38.2, C39.2, C40.2, C41.2, C43.2, C44.2, C45.2, C50.2, C51.2, C52.2, C53.2, C54.2, J1.2, R2.2, R6.2, R13.2, R17.2, R18.1, R18.2, R20.2, R23.2, R25.2, R28.2, R30.2, U1.16, U1.30, U1.31, U1.38, U1.51, U1.61, U1.71, U1.83, U1.94, U1.107, U1.120, U1.130, U1.143, U2.E8, U2.H2, U2.H7, U3.1, U3.3, U3.7, U3.EXP, U5.1, U6.1, U7.2, U8.23, U8.25, U9.9, U10.2, U11.2, U12.2, U13.3, U13.PAD, U14.4, U14.11, U14.17, U15.2, U17.C, U18.1, U18.3, U19.1, U19.3
NET_U1_25: R5.1, U1.25, U19.4
NET_U1_33: C15.1, C16.1, F1.1, U1.32, U1.33
NET_U1_138: R6.1, U1.138
NET_U1_142: U16.3, U16.4
NET_U2_B4: R10.1, U2.B4
NET_U2_B5: R4.1, U2.B5, U18.4
NET_U3_10: C29.1, U3.10
NET_U3_29: R12.1, U3.29
NET_U3_31: R13.1, U3.31
NET_U4_1: U3.4, U4.1
NET_U4_2: U3.2, U4.2
NET_U4_5: U3.6, U4.5
NET_U5_2: C20.1, U5.2
NET_U5_5: C19.1, U5.5
NET_U6_2: C22.1, C23.1, U6.2
NET_U6_5: C21.1, U6.5
NET_U6_13: C22.2, C23.2
NET_U7_1: C24.1, C25.1, C30.1, U3.16, U7.1
NET_U7_15: C24.2, C25.2
NET_U8_1: C33.1, U8.1
NET_U8_2: C33.2, U8.2
NET_U8_3: C35.1, U8.3
NET_U8_22: R14.1, U8.22
NET_U8_24: C32.2, U8.24
NET_U8_27: C34.1, U8.27
NET_U8_28: C32.1, U8.28
NET_U9_3: U8.4, U9.3
NET_U9_4: U8.5, U9.4
NET_U9_5: U8.9, U9.5
NET_U9_6: U8.10, U9.6
NET_U13_1: C39.1, U13.1
NET_U13_6: R16.2, R17.1, U13.6
NET_U13_8: R15.1, U13.8
NET_U14_1: C46.1, R19.1, R20.1, R21.1, R22.1, U14.1, U14.8
NET_U14_2: C45.1, U14.2
NET_U14_3: C46.2, C47.1, C47.2, U14.3
NET_U14_5: R23.1, U14.5
NET_U14_10: C43.1, U14.10
NET_U14_12: C42.1, I1.1, U14.12
NET_U14_14: C42.2, U14.14
NET_U14_15: R24.1, R25.1, U14.15
NET_U14_ATNET_3: I1.2, R19.2
NET_U14_ATNET_4: C47.2, R21.2
NET_U15_1: R27.1, R28.1, U15.1
NET_U15_3: R29.2, R30.1, U15.3
NET_U15_4: R26.1, U15.4, U18.2, U19.2
NET_U16_1: R2.1, U16.1, U16.2
PROC_FMC_A0: U1.10, U2.E2
PROC_FMC_A1: U1.11, U2.D2
PROC_FMC_A2: U1.12, U2.C2
PROC_FMC_A3: U1.13, U2.A2
PROC_FMC_A4: U1.14, U2.B2
PROC_FMC_A5: U1.15, U2.D3
PROC_FMC_A6: U1.50, U2.C3
PROC_FMC_A7: U1.53, U2.A3
PROC_FMC_A8: U1.54, U2.B6
PROC_FMC_A9: U1.55, U2.A6
PROC_FMC_A10: U1.56, U2.C6
PROC_FMC_A11: U1.57, U2.D6
PROC_FMC_A12: U1.87, U2.B7
PROC_FMC_A13: U1.88, U2.A7
PROC_FMC_A14: U1.89, U2.C7
PROC_FMC_A15: U1.90, U2.D7
PROC_FMC_A16: U1.80, U2.E7
PROC_FMC_A17: U1.81, U2.B3
PROC_FMC_A18: U1.82, U2.C4
PROC_FMC_A19: U1.2, U2.D5
PROC_FMC_A20: U1.3, U2.D4
PROC_FMC_A21: U1.4, U2.C5
PROC_FMC_A22: U1.5, U2.B8
PROC_FMC_A23: U1.1, U2.C8
PROC_FMC_D0: U1.85, U2.E3
PROC_FMC_D1: U1.86, U2.H3
PROC_FMC_D2: U1.114, U2.E4
PROC_FMC_D3: U1.115, U2.H4
PROC_FMC_D4: U1.58, U2.H5
PROC_FMC_D5: U1.59, U2.E5
PROC_FMC_D6: U1.60, U2.H6
PROC_FMC_D7: U1.63, U2.E6
PROC_FMC_D8: U1.64, U2.F3
PROC_FMC_D9: U1.65, U2.G3
PROC_FMC_D10: U1.66, U2.F4
PROC_FMC_D11: U1.67, U2.G4
PROC_FMC_D12: U1.68, U2.F5
PROC_FMC_D13: U1.77, U2.G6
PROC_FMC_D14: U1.78, U2.F6
PROC_FMC_D15: U1.79, U2.G7
PROC_FMC_NBL0: R11.1, U1.141, U2.F7
PROC_FMC_NE2: R7.1, U1.124, U2.F2
PROC_FMC_NOE: R8.1, U1.118, U2.G2
PROC_FMC_NWAIT: U1.122, U2.A4
PROC_FMC_NWE: R9.1, U1.119, U2.A5
PROC_I2S2_CK: U1.24, U3.24
PROC_I2S2_EXT_SD: U1.75, U3.25
PROC_I2S2_SD: U1.76, U3.26
PROC_I2S2_WS: U1.73, U3.23
PROC_UART4_RX: U1.112, U8.19
PROC_UART4_TX: U1.111, U8.14
VCC_S1_15V6: C40.1, C44.1, C51.1, C52.1, J1.1, R15.2, R24.2, U13.4, U14.9
VCC_TIER1_1V2: C26.1, C41.1, R16.1, U3.30, U13.5
VCC_TIER1_3V3: C1.1, C2.1, C3.1, C4.1, C5.1, C6.1, C7.1, C8.1, C9.1, C10.1, C11.1, C12.1, C13.1, C14.1, C17.1, C18.1, C27.1, C28.1, C31.1, C36.1, C37.1, C38.1, C50.1, C53.1, C54.1, F1.2, I1.2, R4.2, R5.2, R7.2, R8.2, R9.2, R10.2, R11.2, R12.2, R14.2, R19.2, R26.2, R27.2, R29.1, U1.6, U1.17, U1.39, U1.52, U1.62, U1.72, U1.84, U1.95, U1.108, U1.121, U1.131, U1.144, U2.D8, U2.F1, U2.G5, U3.5, U3.20, U8.26, U10.4, U11.4, U12.4, U15.6, U18.5, U19.5
